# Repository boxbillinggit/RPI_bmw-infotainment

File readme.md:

## Overview

- `gateway/` Source for LIN-bus TCP/IP gateway
- `plugin/` XBMC/KODI-plugins
 - `plugin.service.bmw-infotainment/` Main script for controlling XBMC/KODI through LIN-bus
 - `script.module.bluetooth/` Handles the bluetooth-interface through DBus
- `.gitlab-ci.yml` Configuration file for GitLab CI (continuous integration)
- `__init__.py ` Init script fixing paths when using Python-interpreter in PyCharm (run `__init__`)

## References
 For detailed description -and further instructions, please see [Wiki](http://git.one-infiniteloop.com/larsa/bmw-infotainment/wikis/home).

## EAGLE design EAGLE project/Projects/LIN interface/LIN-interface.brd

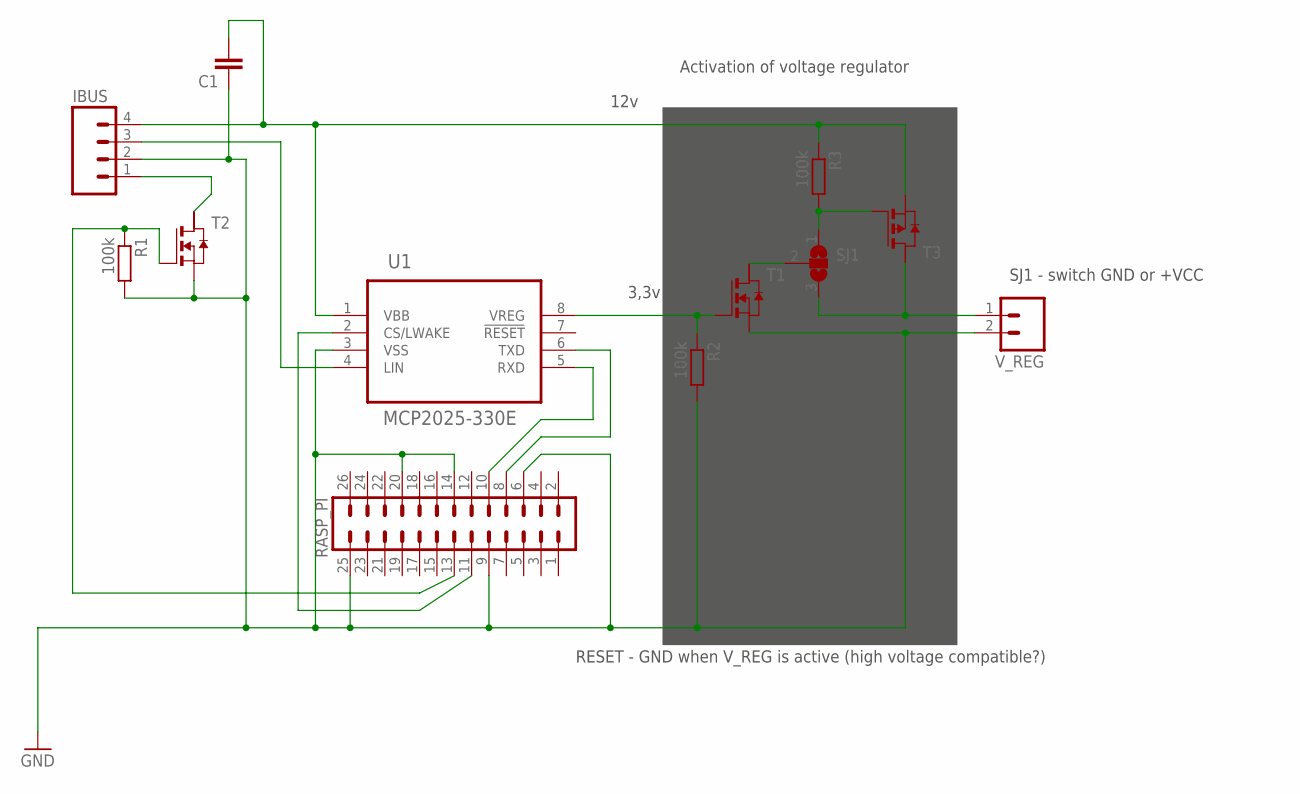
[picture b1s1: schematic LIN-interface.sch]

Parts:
C1: C-EUC1812; C1812
IBUS: M04; 04P
R1, R2, R3: 100k; R5025
RASP_PI: MA13-2MIRRORED; ML26-MIRRORED
SJ1: SJ2W; SJ_2
T1, T2: NMOSSOT223; SOT223
T3: PMOSSOT223; SOT223
U1: MCP2025-330E; DIL08
V_REG: M02; 02P

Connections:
GND: C1.1, IBUS.2, R1.2, R2.2, RASP_PI.6, RASP_PI.9, RASP_PI.14, RASP_PI.20, RASP_PI.25, T1.3 (S), T2.3 (S), U1.3 (VSS), V_REG.2
unnamed: IBUS.3, U1.4 (LIN)
unnamed: SJ1.2, T1.2 (D)
unnamed: RASP_PI.8, U1.6 (TXD)
unnamed: RASP_PI.10, U1.5 (RXD)
unnamed: RASP_PI.11, U1.2 (CS/LWAKE)
unnamed: SJ1.3, T3.2 (D), V_REG.1
unnamed: IBUS.1, T2.2 (D)
unnamed: R3.2, SJ1.1, T3.1 (G)
VBB: C1.2, IBUS.4, R3.1, T3.3 (S), U1.1 (VBB)
VIDEO_ON: R1.1, RASP_PI.13, T2.1 (G)
VREG: R2.1, T1.1 (G), U1.8 (VREG)

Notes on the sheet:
SJ1 - switch GND or +VCC
12v
RESET - GND when V_REG is active (high voltage compatible?)
Activation of voltage regulator
3,3v

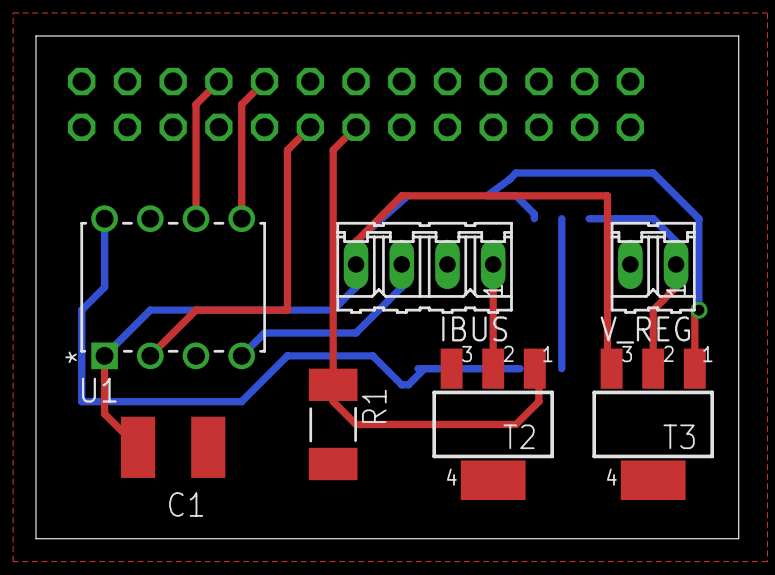
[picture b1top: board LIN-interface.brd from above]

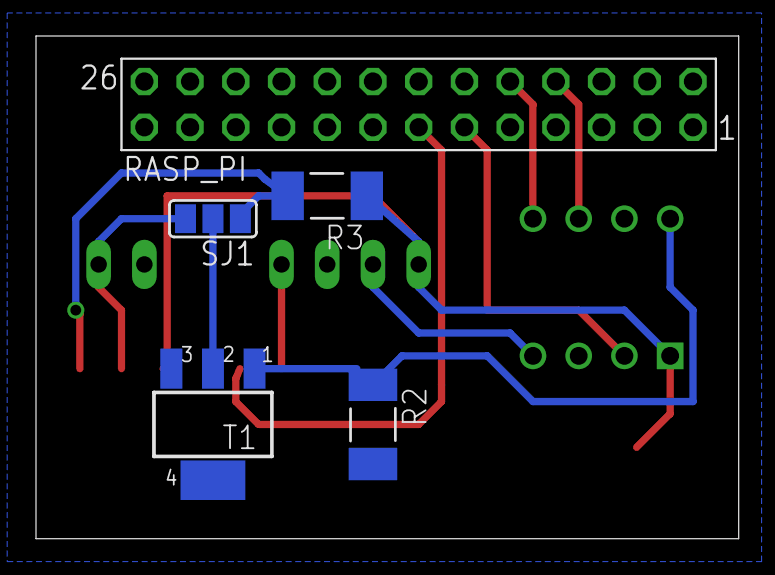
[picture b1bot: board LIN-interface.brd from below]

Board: 2 copper layers, 39.0 x 27.9 mm, 12 parts (5 on the bottom side), 12 nets.

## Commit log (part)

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2015-03-24 test
2015-03-28 Added EAGLE project files
    Complete EAGLE structure moved to GIT repository.
2015-03-29 repository settings.
    added recomended settings
2015-05-08 Repo settings
    Don't track PyCharm settings.
2015-05-08 Repository settings
    Dont track folder ".idea" generated from PyCharm.
2015-05-08 remove igored files
2015-05-10 TCP server up 'n running in KODI :)
2015-05-10 commit all changes
    restructure in folders
2015-05-12 fixed blocking during system shutdown.
2015-05-16 major rework in modules and libs (splitting modules into smaller pieces, rework code completely in TCPdaemon.py)
2015-05-16 Stable (good enough) TCP connection!
2015-05-22 Basic function and structure for keymap is implemented -and tested in XBMC/KODI.
2015-05-25 Add XML signal-database.
2015-07-22 Stable TCP connection, Connect-Disconnect in settings works. NOTE: module is now dependent on cPython plugin (not included in this commit) TODO: need to rework -and rename TCP modules
2015-07-23 Module rework Parsed code to separate classes, amd more..
2015-07-23 Rename modules. Two modules is affected: TCPhandler.py-> TCPIPDaemon.py TCPDaemon.py -> TCPIPSocket.py
2015-07-25 Module keymap - rework on state-machine for buttons. We are now ready for a test in the car :)
2015-07-25 Rename of module keymap.py -> BMButtons.py
2015-07-27 Rework module TCPIPHandler (better overview) Fixed bug in Filter-class (wrong data-types when comparing signal against event-map)
2015-07-27 Fixed fault-handling for XML-database generation.
2015-07-27 Fixed name-conflict in XML-database.
2015-07-27 Rename debug-module This module used outside XBMC, as a XBMC-wrapper
2015-07-27 fixed init bug: "object of type 'NoneType' has no len()"
2015-07-28 Fixed bug for lost reference to rx_buffer when resizing array, causing failure to connect.
2015-07-28 Creating new module for logging. Cleaning in log-messages. Running service in console -or in XBMC makes no different now regarding logmessages. Minor restructure of modules.
2015-07-28 Fixed "Unexpected rx header content" error when parsing TCP/IP-frame buffer containing ping+content
2015-07-28 Fixes issue #6 - reworked logging-module.
2015-08-05 Add deploy-script for Continuous integration. Add repository in settings for automatic updates
2015-08-05 Fixed incorrect name on config file
2015-08-05 Edit .gitlab-ci.yml
    Test CI-build for OpenBM-daemon
2015-08-05 Change Gitlab-ci.yml
    Build -and deploy only for branch master
2015-08-05 Rename path according to standards.
2015-08-05 Commit Netbeans project-files
2015-08-05 relocate folder according to standard.
2015-08-05 Fixed path resolving for modules (paths is now generic and works wherever module is located)
2015-08-08 Rename folder for cPython project
    Yes, I changed the name again :)
2015-08-08 Changing create-repository.py
    Adjusted for Windows deployments (need more rework)
2015-08-08 Netbeans config-files
    adjusted according to previous folder rename
2015-08-09 Deploy foe Windows is working!
2015-08-18 Removing EAGLE-project, not suited for manage in GIT. Using file system as repository instead (http://deploy.one-infiniteloop.com/cadsoft-eagle/)
2015-08-25 Rename folder OpenBM-gateway to gateway
2015-09-13 New plugin - script.module.bluetooth Added new KODI/XBMC module for managing bluetooth stack
2015-11-18 Clean up gateway/ Removing nbproject-files, build-directory, unused files, etc.. Adding cMakeLists.txt (cmake configuration for build)
2015-11-18 modifying readme.md in gateway/
2015-11-18 Added accidentally removed content Added html/ in gateway/
2015-11-18 Add GNU Licence
2015-11-30 Gitlab-CI Modifying configuration-files and create build-scripts for continuous integration
2015-11-30 Fixing config-files for deploy
2015-12-01 Modifying deploy-script
2015-12-01 Change build target path name
2015-12-01 Rename build script for correct target
2015-12-03 add deb-packaging modifying cmake-configurations to build .deb-packages modifying build-scripts to build packages
2015-12-04 Continuous Integration for openbm-gateway established Modifying build-scripts to build .deb-packages Modifying deploy-script
2015-12-04 Sync branches master and Development
2015-12-05 modifying cmake-config files adding git commit has in debian package description for traceability
2015-12-05 Moving files moving create-repository.py to subfolder plugin/ renaming -and moving plugin.module to its plugin subfolder
2015-12-08 updating readme-files
2015-12-08 Moving files, adding new cmake-module all .cpp and .h-sources moved to src/ module cmake-debhelper added
2015-12-09 Modifying deploy-script Publish files accordingly to new path in repository
2015-12-09 Important adjustment for deb-packaging corrected target for html/ installation path added missing cpack config-file for invoking package-script
2015-12-09 Updating readme adjusting readme-files accordingly to modifications in gateway/ deleting old startup conf-file (not used anymore)
2015-12-11 libguicallback moving source-files to sub-directory
2015-12-11 Modifying deploy -and build-scripts major rework of deploy-script for plugins minor changes in build-scripts
2015-12-11 fixing issues for plugin when running in linux update readme build library into corrrect path
2015-12-11 Updating readme-files fixes #3 readme-files in repository and WIKI is currently up-to-date accordingly to projects current status
2015-12-13 Major rework of deploy-script for plugin/ This commit is the last part of #2 and closes #2. Continuous integration is now established for plugin/
2015-12-14 Path-resolution in log.py Fixes path resolution for saving logfiles. Works now on all platforms
2015-12-14 GUI-callback works again! adjusting incorrect reference when calling script which fixes #9 renaming script from default-handler.py to guihandler.py (and fixing its references)
2015-12-14 Fixing default log-settings
2015-12-14 Minor change in debug.xbmc.py fixes translatepath() for running service.py in command-line mode
2015-12-14 Renaming modules in debug/
2015-12-17 Install Script Automatic
2015-12-17 Installation script installs the necessary libraries and starts installations Gateway
2015-12-17 Installation script installs the necessary libraries and starts installations Plugin
2015-12-17 Add init.d Service
2015-12-17 To etc/ibus/ copy form installation
2015-12-17 Update File to use Bootstrap
2015-12-17 Add boostrap css
2015-12-17 Jquery file
2015-12-17 Remove Space
2015-12-19 Initial commit for unit-testing Start fault-tracing performance issues related to #5 by adding test-scripts
2015-12-19 Improvements in XBMC/KODI debugging-interface preparing for test-script
2015-12-19 Gateway-interface for testmodule is working only methods for testing remains now
2015-12-19 Moving xml signal-database class to separate module
2015-12-24 Major rework of modules related to event handling. improved thread-handling, signal-db lookup, state machine for button, etc. known issue left to fix: repeatedly "push-release-push-release" don't wor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
2015-12-24 Unittest added unit tests for Button class and signaldb module
2015-12-25 Minor changes in xml-db and module
2015-12-25 fix index problem for event-list in module events
2015-12-25 Renaming module from IBUSHandler to event_handler
2015-12-25 fixed wrong data format between event-handler and TCP/IP-layer
2015-12-25 Event in XBMC/KODI for pushing right-knob updated "Enter" should be "Select" instead to work properly
2015-12-25 Minor changes in log-module enabling logging to file as default setting.
2015-12-26 Minor changes in modules names, descriptions, docstrings, etc removing not implemented modules
2015-12-26 Moving test_service.py for service event-handling tested OK and this closes #5
2015-12-27 Moving content from module event-handler new module for signal-handling (formerly located in event-handler) hexstring() moved to module log (used in multiple modules when logging)
2015-12-28 Set to daemon-thread from init-function in class instead
2015-12-28 Renaming module for a intuitive overview. from callback.py to gui_events.py
2015-12-29 Update unittest accordingly to previous change in signaldb
2016-01-04 log-format changed changed order in the string for "type" (DEBUG, INFO)
2016-01-04 Major rework of TCP/IP-layer improved thread-handling for TCP/IP, clearer interfaces, cleaner code, better modularization, etc.. added unittests for class Protocol (in module gateway_protocol) some e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
2016-01-06 More improvements in TCP/IP-layer fixes #14 moving callbacks to service-module (better to have callbacks on top-level)
2016-01-06 v1.0.1 - version bump Previous unreleased builds has been tagged as v1.0.0, hence bumping up version for automatic updates to detect this new release!
2016-01-06 Updating descriptions in addon.xml
2016-01-10 Improvements in TCP/IP-layer Implemented a state-machine for tcp-connection
2016-01-10 Cleaner structure in settings
2016-01-10 Minor changes in testmodule gateway
2016-01-14 fixes issue for path-resolution in xbmcaddon debug-module
2016-01-14 Fixes TODO's in signaldb
2016-01-15 fixes TODO's in TCP/IP-protocol
2016-01-16 Minor improvements in event-handling and in signal-db. regexp removed from xml-db using string formatter instead.
2016-01-16 Minor adjustments is xml-db operation names is now shorter adding signal for ignition key status
2016-01-16 Fixing xml signal-db missing attribute improving fault-handling in signaldb.py
2016-01-16 optimizing scroll-speed after test
2016-01-17 improving and optimizing code for cleaner structure
2016-01-17 Implemented bus-statistics Always good to know current bus-activity when tampering with the lin-bus (IBUS) Adding signals for reading current MID-state (not validated, only theoretical at the moment)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
2016-01-17 Improvements in welcome-text, event-handler, etc.. welcome-text showing once if ignition is on -or turns on (callback implemented) state-machine now in separate module, since it's used in many places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
2016-01-18 Minor improvement in event-handler (possible future bug)
2016-01-18 Improving interfaces against modules
2016-01-22 New structure in xml signaldb clearer structure, etc.. updating unittest accordingly.
2016-01-22 Minor improvements in code-structure
2016-01-22 enable/disable welcome-text implemented
2016-01-22 v1.0.2 - version bump
2016-01-22 minor changes in tests/gateway.py
2016-01-30 fixing to-do
2016-01-30 New script for packaging plugin adjusting continuous integration-config file accordingly
2016-01-30 Fixes #1 CD-polling now implemented Polling implemented in plugin instead which is better strategically. removing system shutdown control from plugin, now controlled from gateway event-file instead (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
2016-03-05 Adding option in settings option for writing bus-activity to logger
2016-03-05 Minor change in event-handler try-except removed becuse it hide stack-trace during errors
2016-03-05 New feature in statemachine Feature currently not used, but maybe in the future!
2016-03-06 New implementations CDChanger emulator implemented default GUI added State-machine for current BMBT-state implemented, screen and controls is active only in state CDChanger Improved welcome-text hand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
2016-03-06 v1.0.3 - version bump
2016-03-06 Fixes bug for creating zip-archive
2016-03-06 Fixes bug for building zip-archive archive was put in wrong path
2016-03-06 Renaming deploy.py to publish.py
2016-03-06 Fixes problem in window-default.xml Background image does not always loads correctly
2016-03-19 Improved notification-handling for disconnect/connect Notifies if disconnected, then notifies when connected again (not repeatedly for each try)
2016-03-19 Fix todo - notify on system shutdown
2016-03-20 Improvements for state CD-changer flush index area when entering CDC-state (removing CD-changer buttons)
2016-03-23 Added feature: GPIO control of RCA-input (screen) Possible fix for #22 (note: not tested on target)
2016-03-27 Test Blinking
2016-03-27 Update to GPIO RPi
2016-03-30 Testing Close and open Mirror
    Witch remote Buttons
2016-03-30 Update to Mirror
2016-03-31 Update SignalDB
2016-03-31 Update Signal Mirror
2016-04-04 Testing send command
2016-04-04 Update bug
2016-04-04 Get from ike ign-key
2016-04-05 Create gh-pages branch via GitHub
2016-04-07 Eqhm
